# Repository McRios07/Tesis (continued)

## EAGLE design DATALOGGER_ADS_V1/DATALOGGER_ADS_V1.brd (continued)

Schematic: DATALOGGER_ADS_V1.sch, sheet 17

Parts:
C99, C103: 10uF; C0603
C100: 100uF; C1206
C101, C102, C104: 0.1uF; C0603
C116, C117: 1uF; C0603
R134, R136: 1K; R0603
R135, R138: 100; R0603
U7, U8: OPA350EA/2K5; DGK8_TEX
U12: REF5025AID; D8

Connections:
+5V: C117.1, U7.7 (V+), U8.7 (V+), U12.2 (VIN); also elsewhere on the board
GND: C99.2, C100.2, C102.2, C103.2, C104.2, C116.2, C117.2, U7.4 (V-), U8.4 (V-), U12.4 (GND); also elsewhere on the board
unnamed: C99.1, R134.1, U12.6 (VOUT)
unnamed: C100.1, R134.2, U7.3 (IN+)
unnamed: C116.1, U12.5 (TRIM/NR)
unnamed: C101.1, R136.1, U7.2 (IN-)
unnamed: C101.2, R135.1, U7.6 (OUTPUT)
unnamed: R138.1, U8.2 (IN-), U8.6 (OUTPUT)
VCOM3: R138.2; also elsewhere on the board
VCOMM3: C104.1, U8.3 (IN+); also elsewhere on the board
VREFP3: C102.1, C103.1, R135.2, R136.2; also elsewhere on the board

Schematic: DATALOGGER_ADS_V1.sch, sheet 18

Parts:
C105, C106, C107: 10uF; C0603
U9: ADS1278IPAPR; PAP64_7X7

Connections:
+1V8: C107.1, U9.26 (DVDD); also elsewhere on the board
+3V3: C106.1, U9.10 (CLKDIV_2), U9.22 (IOVDD_2), U9.23 (IOVDD), U9.31 (FORMAT1), U9.35 (!PWDN8), U9.36 (!PWDN7), U9.37 (!PWDN6), U9.38 (!PWDN5), U9.39 (!PWDN4), U9.40 (!PWDN3), U9.41 (!PWDN2), U9.42 (!PWDN1); also elsewhere on the board
+5V: C105.1, U9.5 (AVDD_2), U9.44 (AVDD_3), U9.53 (AVDD_4), U9.60 (AVDD); also elsewhere on the board
AINN3_1: U9.4 (AINN1); also elsewhere on the board
AINN3_2: U9.2 (AINN2); also elsewhere on the board
AINN3_3: U9.64 (AINN3); also elsewhere on the board
AINN3_4: U9.62 (AINN4); also elsewhere on the board
AINN3_5: U9.52 (AINN5)
AINN3_6: U9.50 (AINN6)
AINN3_7: U9.48 (AINN7)
AINN3_8: U9.46 (AINN8)
AINP3_1: U9.3 (AINP1); also elsewhere on the board
AINP3_2: U9.1 (AINP2); also elsewhere on the board
AINP3_3: U9.63 (AINP3); also elsewhere on the board
AINP3_4: U9.61 (AINP4); also elsewhere on the board
AINP3_5: U9.51 (AINP5)
AINP3_6: U9.49 (AINP6)
AINP3_7: U9.47 (AINP7)
AINP3_8: U9.45 (AINP8)
CLK3: U9.27 (CLKDIV); also elsewhere on the board
DOUT3_1: U9.20 (DOUT1); also elsewhere on the board
DOUT3_2: U9.19 (DOUT2); also elsewhere on the board
DOUT3_3: U9.18 (DOUT3); also elsewhere on the board
DOUT3_4: U9.17 (DOUT4); also elsewhere on the board
DOUT3_5: U9.16 (DOUT5)
DOUT3_6: U9.15 (DOUT6)
DOUT3_7: U9.14 (DOUT7)
DOUT3_8: U9.13 (DOUT8)
DRDY3: U9.29 (!DRDY/FSYNC); also elsewhere on the board
GND: C105.2, C106.2, C107.2, U9.6 (AGND_2), U9.7 (DGND_2), U9.8 (TEST0), U9.9 (TEST1), U9.12 (DIN), U9.21 (DGND_3), U9.24 (DGND_4), U9.25 (DGND), U9.30 (FORMAT2), U9.32 (FORMAT0), U9.33 (MODE1), U9.34 (MODE0), U9.43 (AGND_3), U9.54 (AGND_4), U9.57 (VREFN), U9.58 (AGND_5), U9.59 (AGND), U9.65 (EPAD); also elsewhere on the board
SCLK3: U9.28 (SCLK); also elsewhere on the board
SYNC3: U9.11 (!SYNC); also elsewhere on the board
VCOMM3: U9.55 (VCOM); also elsewhere on the board
VREFP3: U9.56 (VREFP); also elsewhere on the board

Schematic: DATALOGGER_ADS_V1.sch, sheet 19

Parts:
IC35, IC36, IC37, IC38, IC39, IC40, IC41, IC42: FODM217DV; SOIC127P700X220-4N
J3: 1985027
R147, R148, R149, R150, R151, R152, R153, R154, R155, R156, R157, R158, R159, R160, R161, R162: 220R; R0805

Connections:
+3V3: R148.2, R150.2, R152.2, R154.2, R156.2, R158.2, R160.2, R162.2; also elsewhere on the board
+5V: R147.1, R149.1, R151.1, R153.1, R155.1, R157.1, R159.1, R161.1; also elsewhere on the board
GND: IC35.3 (EMITTER), IC36.3 (EMITTER), IC37.3 (EMITTER), IC38.3 (EMITTER), IC39.3 (EMITTER), IC40.3 (EMITTER), IC41.3 (EMITTER), IC42.3 (EMITTER); also elsewhere on the board
LAZO1: IC35.4 (COLLECTOR), R148.1; also elsewhere on the board
LAZO2: IC36.4 (COLLECTOR), R150.1; also elsewhere on the board
LAZO3: IC37.4 (COLLECTOR), R152.1; also elsewhere on the board
LAZO4: IC38.4 (COLLECTOR), R154.1; also elsewhere on the board
LAZO5: IC39.4 (COLLECTOR), R156.1; also elsewhere on the board
LAZO6: IC40.4 (COLLECTOR), R158.1; also elsewhere on the board
LAZO7: IC41.4 (COLLECTOR), R160.1; also elsewhere on the board
LAZO8: IC42.4 (COLLECTOR), R162.1; also elsewhere on the board
LOOP1: IC35.2 (CATHODE), J3.1
LOOP2: IC36.2 (CATHODE), J3.2
LOOP3: IC37.2 (CATHODE), J3.3
LOOP4: IC38.2 (CATHODE), J3.4
LOOP5: IC39.2 (CATHODE), J3.5
LOOP6: IC40.2 (CATHODE), J3.6
LOOP7: IC41.2 (CATHODE), J3.7
LOOP8: IC42.2 (CATHODE), J3.8
unnamed: IC35.1 (ANODE), R147.2
unnamed: IC36.1 (ANODE), R149.2
unnamed: IC37.1 (ANODE), R151.2
unnamed: IC38.1 (ANODE), R153.2
unnamed: IC39.1 (ANODE), R155.2
unnamed: IC40.1 (ANODE), R157.2
unnamed: IC41.1 (ANODE), R159.2
unnamed: IC42.1 (ANODE), R161.2

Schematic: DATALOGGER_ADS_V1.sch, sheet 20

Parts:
IC31, IC32, IC33, IC34: TLV2771CDBVR; SOT95P280X145-5N
J4: 1989764; CONN_1989764_PXC
R49, R103, R133, R137: 50M; R0805
R53, R107, R164, R165: 1K; R0805
R143, R144, R145, R146: 100M; R0805

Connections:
+3V3: IC31.5 (VDD), IC32.5 (VDD), IC33.5 (VDD), IC34.5 (VDD); also elsewhere on the board
DOBLE1: IC31.3 (IN+), J4.1, R143.1
DOBLE2: IC32.3 (IN+), J4.2, R144.1
DOBLE3: IC33.3 (IN+), J4.3, R145.1
DOBLE4: IC34.3 (IN+), J4.4, R146.1
GND: IC31.2 (GND), IC32.2 (GND), IC33.2 (GND), IC34.2 (GND), R53.1, R107.1, R143.2, R144.2, R145.2, R146.2, R164.1, R165.1; also elsewhere on the board
INPUT17+: IC31.1 (OUT), R49.2; also elsewhere on the board
INPUT18+: IC32.1 (OUT), R103.2; also elsewhere on the board
INPUT19+: IC33.1 (OUT), R133.2; also elsewhere on the board
INPUT20+: IC34.1 (OUT), R137.2; also elsewhere on the board
unnamed: IC33.4 (IN-), R133.1, R165.2
unnamed: IC31.4 (IN-), R49.1, R53.2
unnamed: IC32.4 (IN-), R103.1, R107.2
unnamed: IC34.4 (IN-), R137.1, R164.2

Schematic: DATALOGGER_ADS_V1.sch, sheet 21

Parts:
IC27: D36V28F5-5V-3.2A
IC28: D24V5F1-1.8V-500MA; D24V5F1
IC29: D24V10F3-3.3V-1A
IC30, IC43: D24V25F5-5V-2.5A
J5: 1755736; CONN_1924305
U$4: D24V22F12-12V-2.2A; D24V22F12

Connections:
5V_2.5A: IC30.VOUT; also elsewhere on the board
5V_3.2A: IC27.6 (VOUT); also elsewhere on the board
+1V8: IC28.4 (VOUT); also elsewhere on the board
+3V3: IC29.5 (VOUT); also elsewhere on the board
+5V: IC43.VOUT; also elsewhere on the board
+12V: U$4.5 (VOUT); also elsewhere on the board
+24V: IC27.3 (VIN), IC28.2 (VIN), IC29.3 (VIN), IC30.VIN, IC43.VIN, J5.1, U$4.3 (VIN)
GND: IC27.4 (GND), IC27.5 (GND), IC28.3 (GND), IC29.4 (GND), IC30.GND@3 (GND), IC30.GND@4 (GND), IC43.GND@3 (GND), IC43.GND@4 (GND), J5.2, U$4.4 (GND); also elsewhere on the board

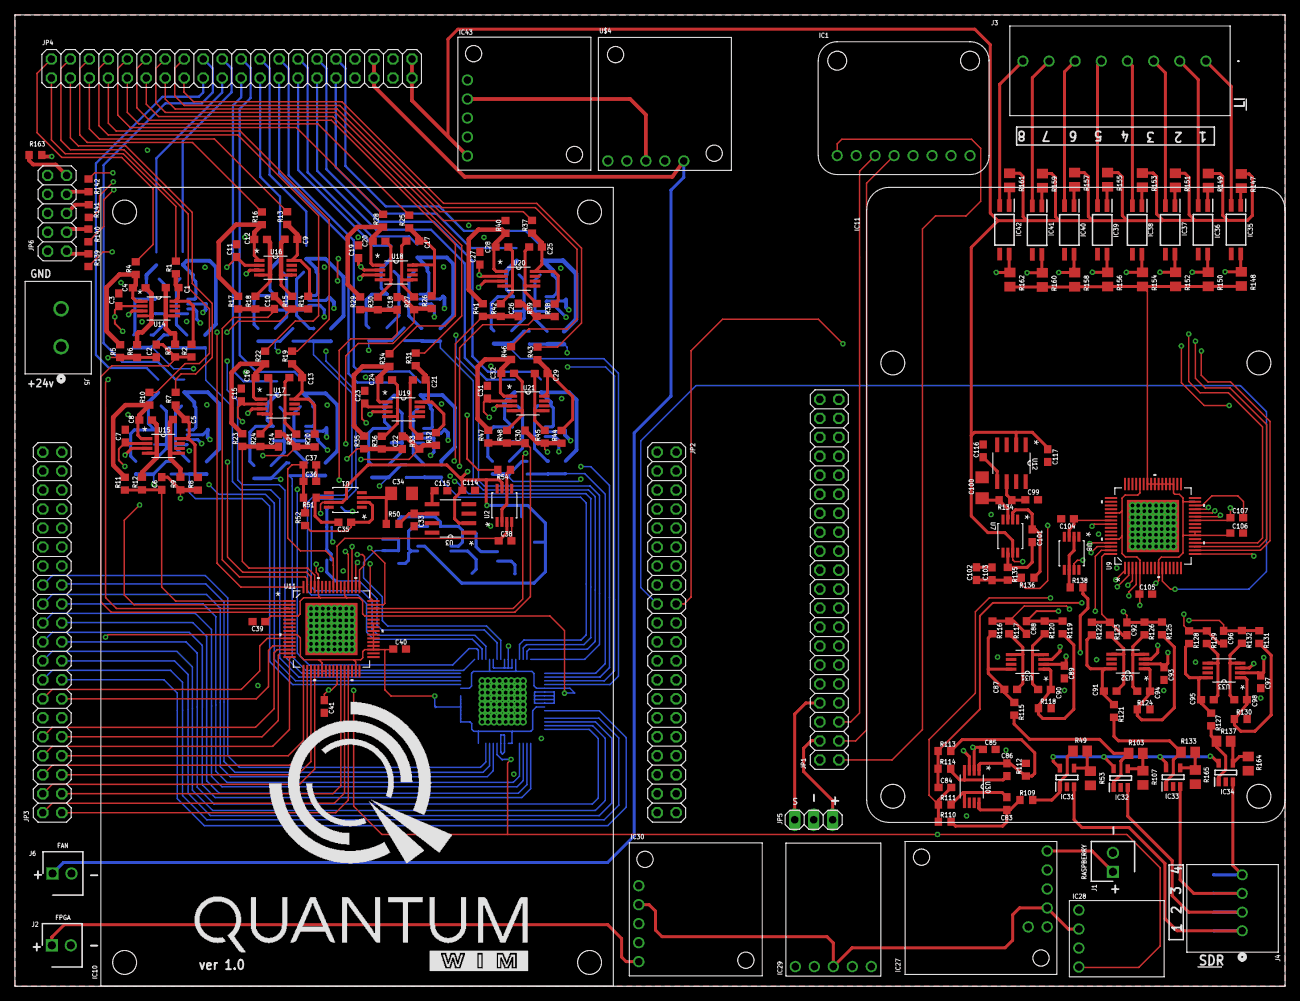
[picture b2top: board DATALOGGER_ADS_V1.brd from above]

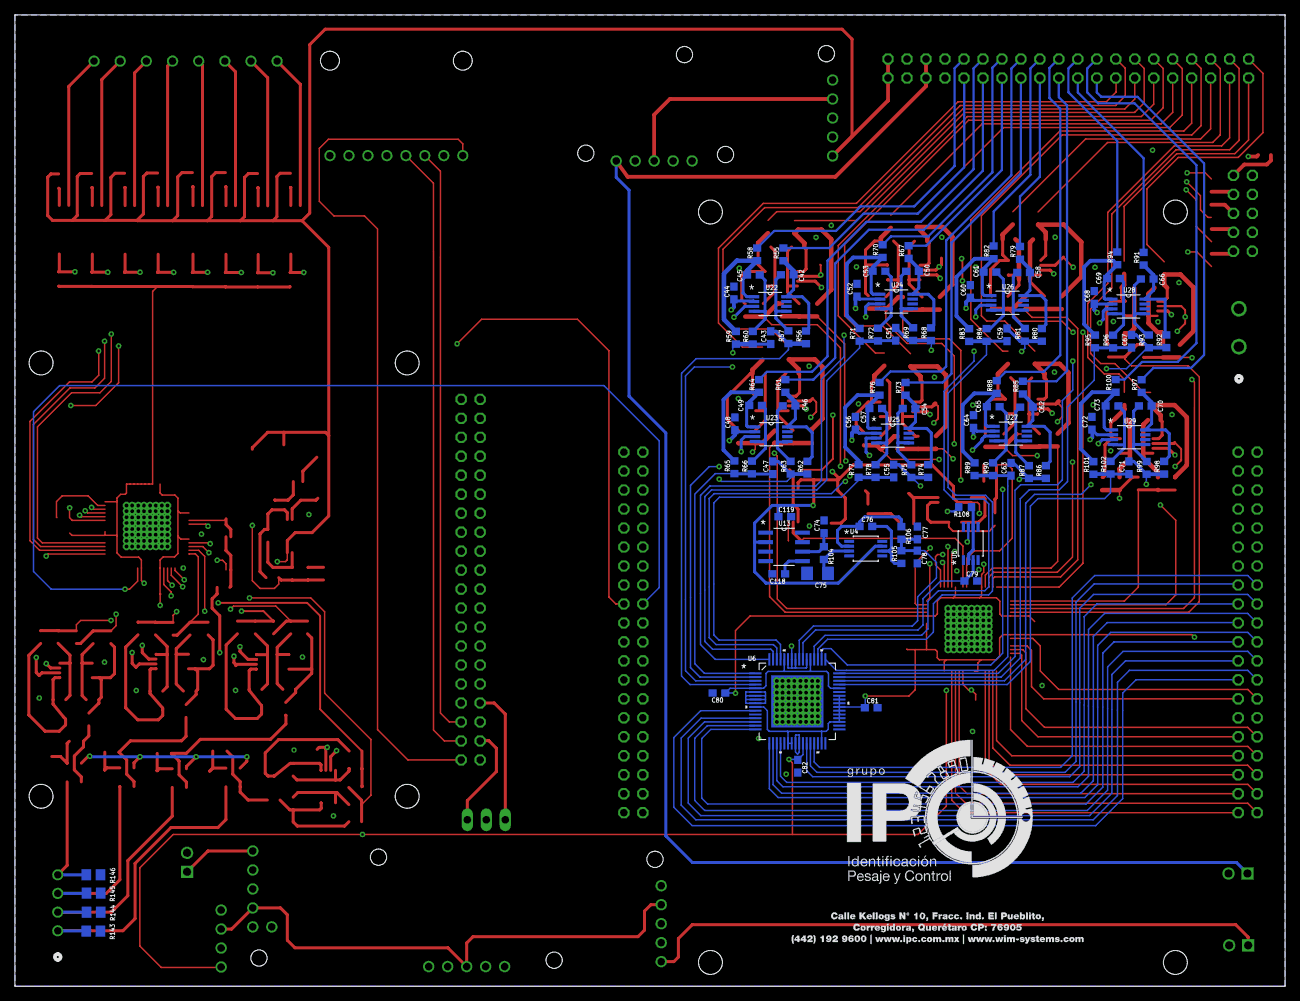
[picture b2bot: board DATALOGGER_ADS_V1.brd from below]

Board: 4 copper layers, 170.0 x 130.0 mm, 343 parts (111 on the bottom side), 269 nets.

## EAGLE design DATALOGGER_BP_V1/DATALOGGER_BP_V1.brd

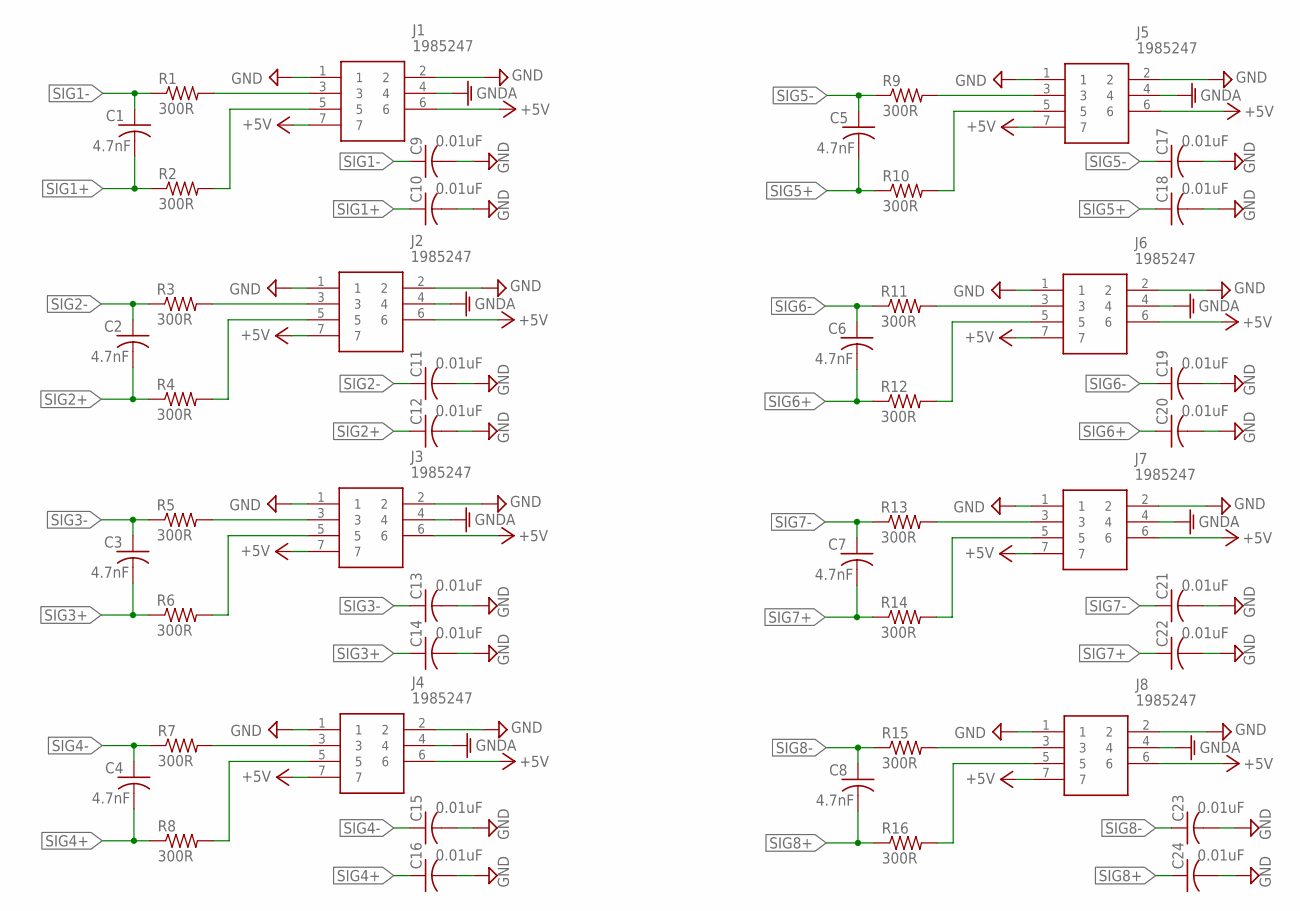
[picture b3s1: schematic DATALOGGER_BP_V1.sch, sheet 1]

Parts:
C1, C2, C3, C4, C5, C6, C7, C8: 4.7nF; C0805
C9, C10, C11, C12, C13, C14, C15, C16, C17, C18, C19, C20, C21, C22, C23, C24: 0.01uF; C0805
J1, J2, J3, J4, J5, J6, J7, J8: 1985247
R1, R2, R3, R4, R5, R6, R7, R8, R9, R10, R11, R12, R13, R14, R15, R16: 300R; R0805

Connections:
+5V: J1.6, J1.7, J2.6, J2.7, J3.6, J3.7, J4.6, J4.7, J5.6, J5.7, J6.6, J6.7, J7.6, J7.7, J8.6, J8.7; also elsewhere on the board
GND: C9.2, C10.2, C11.2, C12.2, C13.2, C14.2, C15.2, C16.2, C17.2, C18.2, C19.2, C20.2, C21.2, C22.2, C23.2, C24.2, J1.1, J1.2, J2.1, J2.2, J3.1, J3.2, J4.1, J4.2, J5.1, J5.2, J6.1, J6.2, J7.1, J7.2, J8.1, J8.2; also elsewhere on the board
GNDA: J1.4, J2.4, J3.4, J4.4, J5.4, J6.4, J7.4, J8.4; also elsewhere on the board
unnamed: J1.3, R1.2
unnamed: J1.5, R2.2
unnamed: J2.3, R3.2
unnamed: J2.5, R4.2
unnamed: J3.3, R5.2
unnamed: J3.5, R6.2
unnamed: J4.3, R7.2
unnamed: J4.5, R8.2
unnamed: J5.3, R9.2
unnamed: J5.5, R10.2
unnamed: J6.3, R11.2
unnamed: J6.5, R12.2
unnamed: J7.3, R13.2
unnamed: J7.5, R14.2
unnamed: J8.3, R15.2
unnamed: J8.5, R16.2
SIG1+: C1.2, C10.1, R2.1; also elsewhere on the board
SIG1-: C1.1, C9.1, R1.1; also elsewhere on the board
SIG2+: C2.2, C12.1, R4.1; also elsewhere on the board
SIG2-: C2.1, C11.1, R3.1; also elsewhere on the board
SIG3+: C3.2, C14.1, R6.1; also elsewhere on the board
SIG3-: C3.1, C13.1, R5.1; also elsewhere on the board
SIG4+: C4.2, C16.1, R8.1; also elsewhere on the board
SIG4-: C4.1, C15.1, R7.1; also elsewhere on the board
SIG5+: C5.2, C18.1, R10.1; also elsewhere on the board
SIG5-: C5.1, C17.1, R9.1; also elsewhere on the board
SIG6+: C6.2, C20.1, R12.1; also elsewhere on the board
SIG6-: C6.1, C19.1, R11.1; also elsewhere on the board
SIG7+: C7.2, C22.1, R14.1; also elsewhere on the board
SIG7-: C7.1, C21.1, R13.1; also elsewhere on the board
SIG8+: C8.2, C24.1, R16.1; also elsewhere on the board
SIG8-: C8.1, C23.1, R15.1; also elsewhere on the board

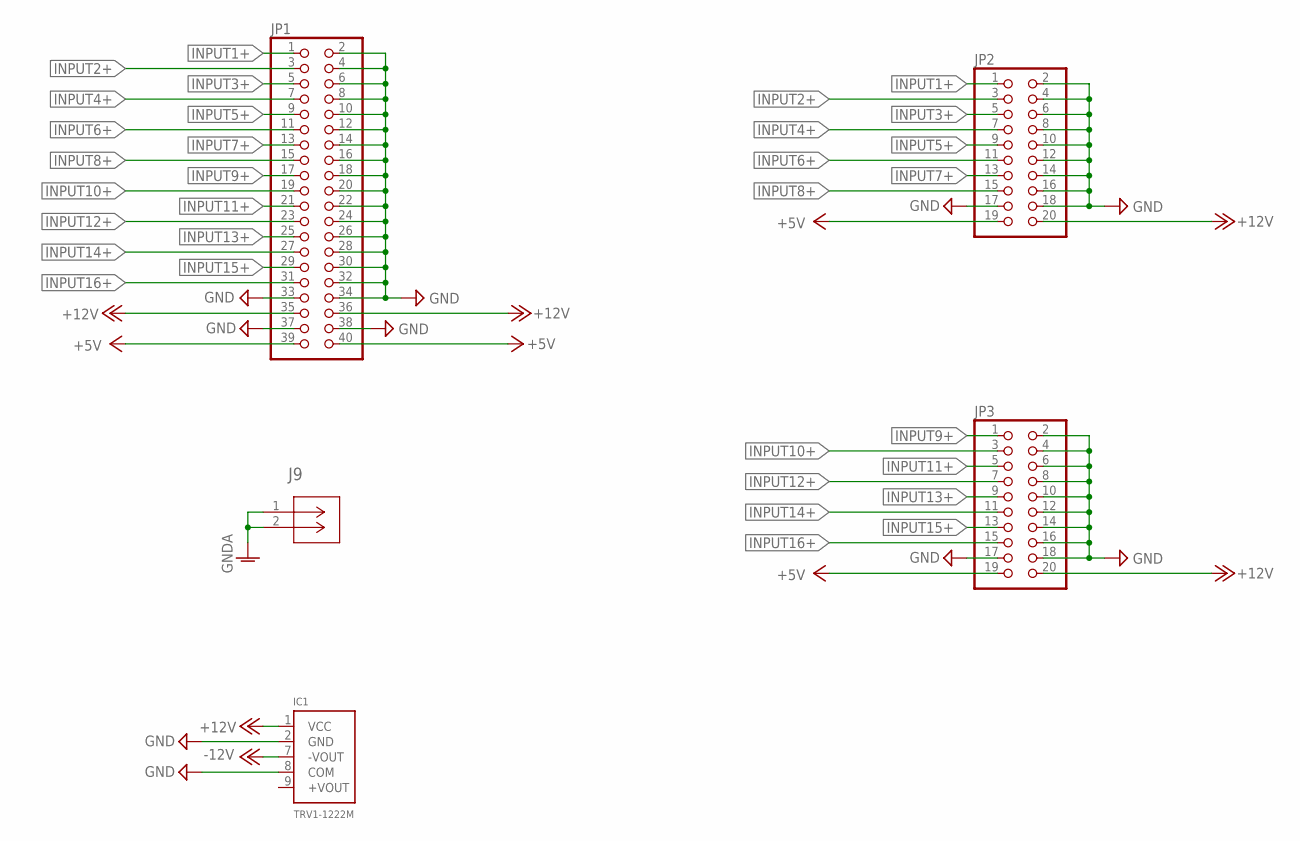
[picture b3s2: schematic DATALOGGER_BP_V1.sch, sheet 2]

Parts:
IC1: TRV1-1222M
J9: 1755736; CONN_1924305
JP1: PINHD-2X20; 2X20
JP2, JP3: PINHD-2X10; 2X10

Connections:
+5V: JP1.39, JP1.40, JP2.19, JP3.19; also elsewhere on the board
+12V: IC1.1 (VCC), JP1.35, JP1.36, JP2.20, JP3.20; also elsewhere on the board
-12V: IC1.7 (-VOUT); also elsewhere on the board
GND: IC1.2 (GND), IC1.8 (COM), JP1.2, JP1.4, JP1.6, JP1.8, JP1.10, JP1.12, JP1.14, JP1.16, JP1.18, JP1.20, JP1.22, JP1.24, JP1.26, JP1.28, JP1.30, JP1.32, JP1.33, JP1.34, JP1.37, JP1.38, JP2.2, JP2.4, JP2.6, JP2.8, JP2.10, JP2.12, JP2.14, JP2.16, JP2.17, JP2.18, JP3.2, JP3.4, JP3.6, JP3.8, JP3.10, JP3.12, JP3.14, JP3.16, JP3.17, JP3.18; also elsewhere on the board
GNDA: J9.1, J9.2; also elsewhere on the board
INPUT1+: JP1.1, JP2.1; also elsewhere on the board
INPUT2+: JP1.3, JP2.3; also elsewhere on the board
INPUT3+: JP1.5, JP2.5; also elsewhere on the board
INPUT4+: JP1.7, JP2.7; also elsewhere on the board
INPUT5+: JP1.9, JP2.9; also elsewhere on the board
INPUT6+: JP1.11, JP2.11; also elsewhere on the board
INPUT7+: JP1.13, JP2.13; also elsewhere on the board
INPUT8+: JP1.15, JP2.15; also elsewhere on the board
INPUT9+: JP1.17, JP3.1
INPUT10+: JP1.19, JP3.3
INPUT11+: JP1.21, JP3.5
INPUT12+: JP1.23, JP3.7
INPUT13+: JP1.25, JP3.9
INPUT14+: JP1.27, JP3.11
INPUT15+: JP1.29, JP3.13
INPUT16+: JP1.31, JP3.15

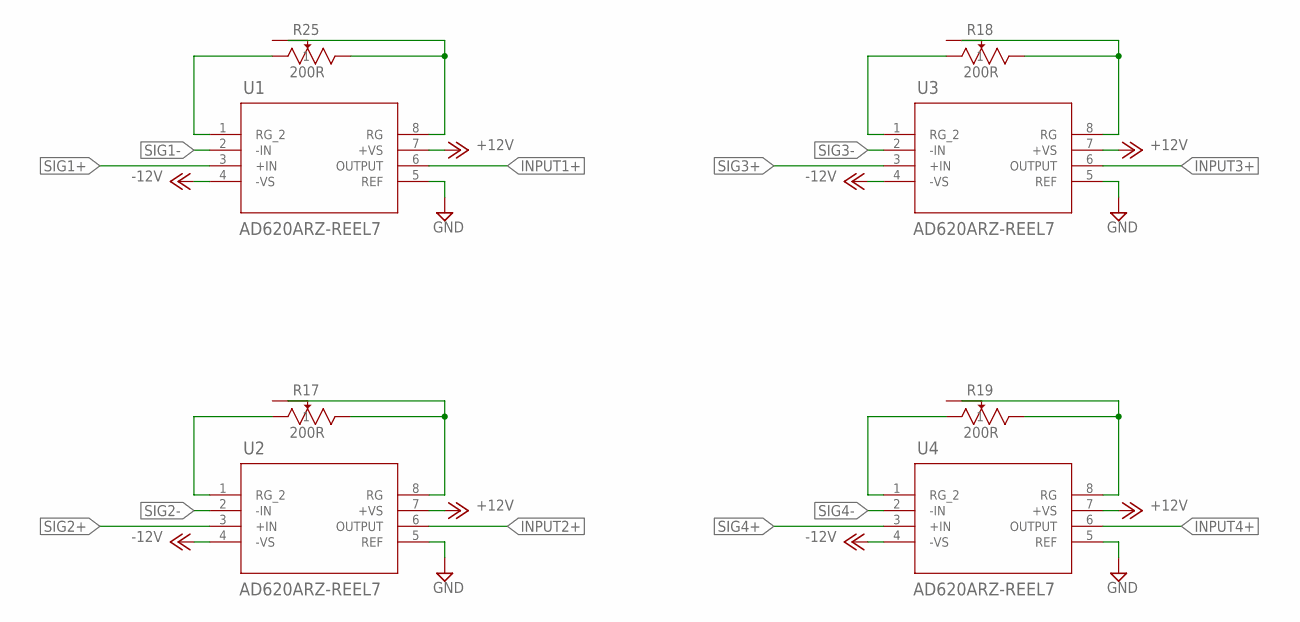
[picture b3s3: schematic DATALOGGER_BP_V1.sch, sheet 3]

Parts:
R17, R18, R19, R25: 200R; RES3_22A_TTE
U1, U2, U3, U4: AD620ARZ-REEL7; R_8_ADI

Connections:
+12V: U1.7 (+VS), U2.7 (+VS), U3.7 (+VS), U4.7 (+VS); also elsewhere on the board
-12V: U1.4 (-VS), U2.4 (-VS), U3.4 (-VS), U4.4 (-VS); also elsewhere on the board
GND: U1.5 (REF), U2.5 (REF), U3.5 (REF), U4.5 (REF); also elsewhere on the board
INPUT1+: U1.6 (OUTPUT); also elsewhere on the board
INPUT2+: U2.6 (OUTPUT); also elsewhere on the board
INPUT3+: U3.6 (OUTPUT); also elsewhere on the board
INPUT4+: U4.6 (OUTPUT); also elsewhere on the board
unnamed: R25.1, U1.1 (RG_2)
unnamed: R25.2, R25.3, U1.8 (RG)
unnamed: R17.1, U2.1 (RG_2)
unnamed: R17.2, R17.3, U2.8 (RG)
unnamed: R18.1, U3.1 (RG_2)
unnamed: R18.2, R18.3, U3.8 (RG)
unnamed: R19.1, U4.1 (RG_2)
unnamed: R19.2, R19.3, U4.8 (RG)
SIG1+: U1.3 (+IN); also elsewhere on the board
SIG1-: U1.2 (-IN); also elsewhere on the board
SIG2+: U2.3 (+IN); also elsewhere on the board
SIG2-: U2.2 (-IN); also elsewhere on the board
SIG3+: U3.3 (+IN); also elsewhere on the board
SIG3-: U3.2 (-IN); also elsewhere on the board
SIG4+: U4.3 (+IN); also elsewhere on the board
SIG4-: U4.2 (-IN); also elsewhere on the board

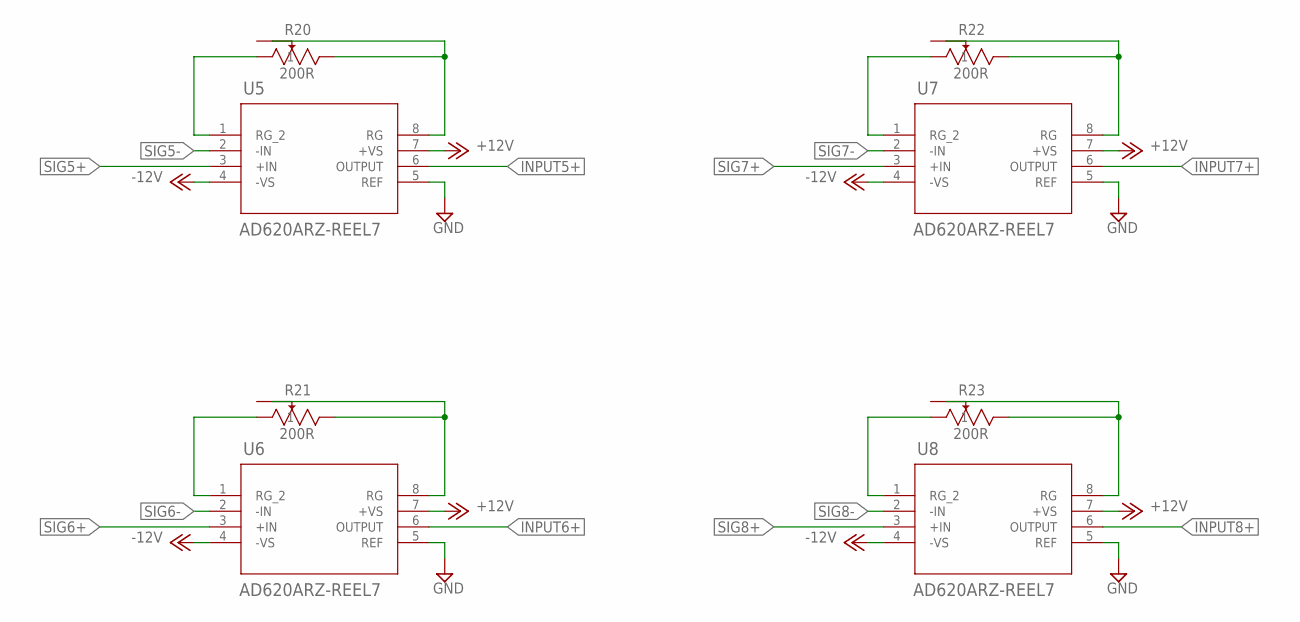
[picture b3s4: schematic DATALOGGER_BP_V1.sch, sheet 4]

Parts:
R20, R21, R22, R23: 200R; RES3_22A_TTE
U5, U6, U7, U8: AD620ARZ-REEL7; R_8_ADI

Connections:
+12V: U5.7 (+VS), U6.7 (+VS), U7.7 (+VS), U8.7 (+VS); also elsewhere on the board
-12V: U5.4 (-VS), U6.4 (-VS), U7.4 (-VS), U8.4 (-VS); also elsewhere on the board
GND: U5.5 (REF), U6.5 (REF), U7.5 (REF), U8.5 (REF); also elsewhere on the board
INPUT5+: U5.6 (OUTPUT); also elsewhere on the board
INPUT6+: U6.6 (OUTPUT); also elsewhere on the board
INPUT7+: U7.6 (OUTPUT); also elsewhere on the board
INPUT8+: U8.6 (OUTPUT); also elsewhere on the board
unnamed: R20.1, U5.1 (RG_2)
unnamed: R20.2, R20.3, U5.8 (RG)
unnamed: R21.1, U6.1 (RG_2)
unnamed: R21.2, R21.3, U6.8 (RG)
unnamed: R22.1, U7.1 (RG_2)
unnamed: R22.2, R22.3, U7.8 (RG)
unnamed: R23.1, U8.1 (RG_2)
unnamed: R23.2, R23.3, U8.8 (RG)
SIG5+: U5.3 (+IN); also elsewhere on the board
SIG5-: U5.2 (-IN); also elsewhere on the board
SIG6+: U6.3 (+IN); also elsewhere on the board
SIG6-: U6.2 (-IN); also elsewhere on the board
SIG7+: U7.3 (+IN); also elsewhere on the board
SIG7-: U7.2 (-IN); also elsewhere on the board
SIG8+: U8.3 (+IN); also elsewhere on the board
SIG8-: U8.2 (-IN); also elsewhere on the board

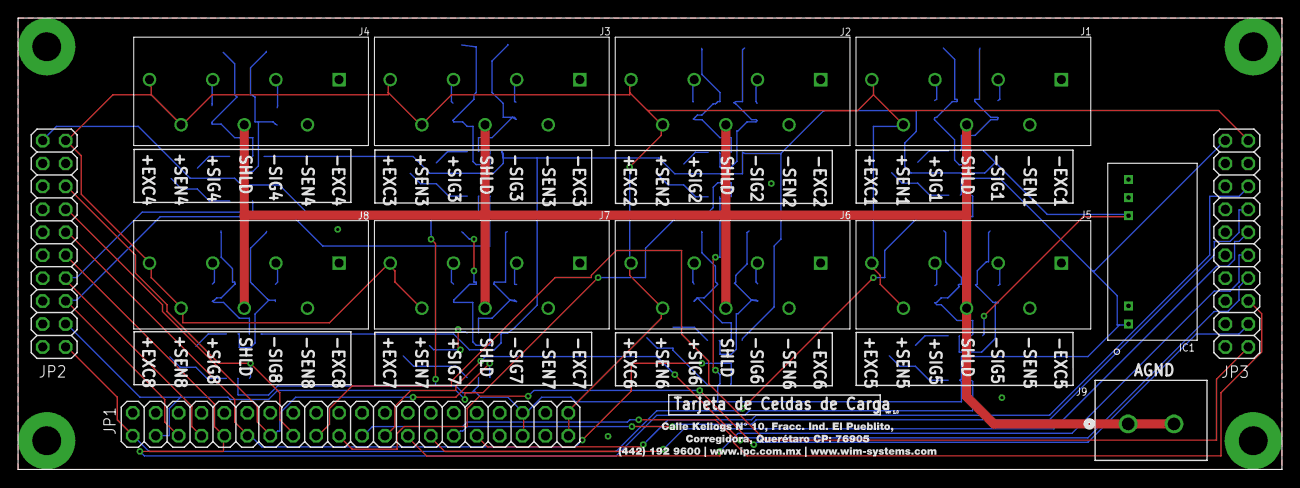
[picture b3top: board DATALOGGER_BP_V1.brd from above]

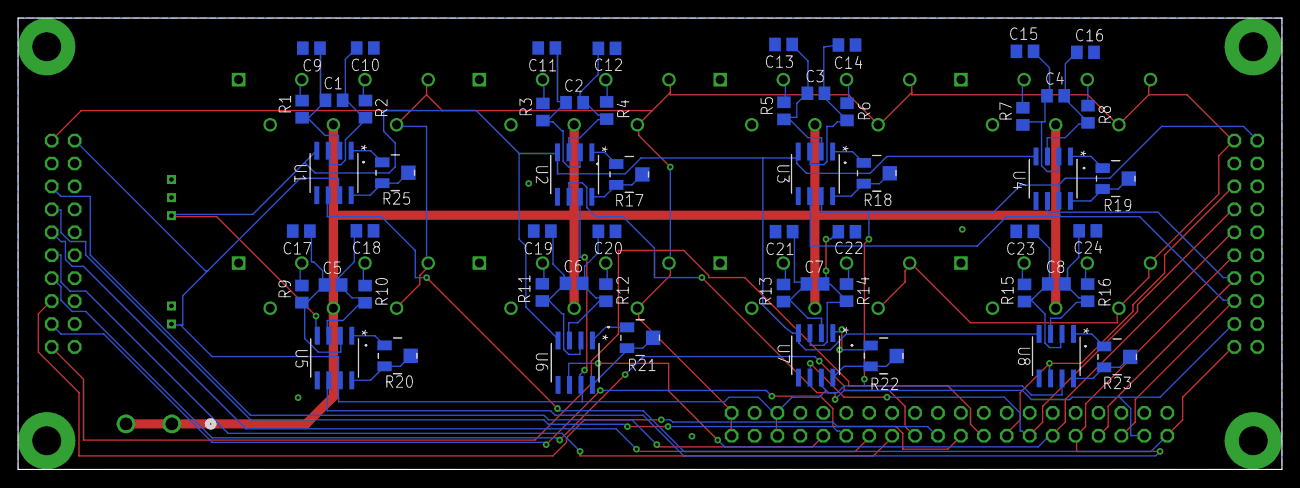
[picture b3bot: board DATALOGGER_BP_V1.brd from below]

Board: 2 copper layers, 140.0 x 50.0 mm, 69 parts (56 on the bottom side), 69 nets.

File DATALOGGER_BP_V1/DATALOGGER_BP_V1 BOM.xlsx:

|  |  | DATALOGGER_BP_V1 BOM
Item # | *Designator | *Qty | Manufacturer | *Mfg Part # | Description / Value | *Package/Footprint | Type | Your Instructions / Notes
1 | JP2, JP3 | 2 | Generic | Generic | Pin header | 2X10 | PTH
2 | JP1 | 1 | Generic | Generic | Pin header | 2X20 | PTH
3 | C1, C2, C3, C4, C5, C6, C7, C8 | 8 | Würth Elektronik | 885012207037 | 4700pF ±10% 16V Ceramic Capacitor X7R 0805 (2012 Metric) | 0805 | SMD | https://www.digikey.com/en/products/detail/w%C3%BCrth-elektr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
4 | R1, R2, R3, R4, R5, R6, R7, R8, R9, R10, R11, R12, R13, R14, R15, R16 | 16 | Yageo | RC0805FR-07300RL | 300 Ohms ±1% 0.125W, 1/8W Chip Resistor 0805 (2012 Metric) Moisture Resistant T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 | 0805 | SMD | https://www.digikey.com/en/products/detail/yageo/RC0805FR-07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
5 | C9, C10, C11, C12, C13, C14, C15, C16, C17, C18, C19, C20, C21, C22, C23, C24 | 16 | Würth Elektronik | 885012007009 | 10000pF ±5% 10V Ceramic Capacitor C0G, NP0 0805 (2012 Metric) | 0805 | SMD | https://www.digikey.com/en/products/detail/w%C3%BCrth-elektr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
6 | J1, J2, J3, J4, J5, J6, J7, J7 | 8 | Phoenix Contact | 1985247 | TERM BLOCK 7POS 45DEG 3.5MM PCB | 1985247 | PTH | https://www.digikey.com.mx/en/products/detail/phoenix-contac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
7 | R17, R18, R19, R20, R21, R22, R23, R25 | 8 | TT Electronics/BI | 22AR200LFTR | TRIMMER 200OHM 0.125W J LEAD TOP |  | SMD | https://www.digikey.com.mx/es/products/detail/tt-electronics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
8 | U1, U2, U3, U4, U5, U6, U7, U8 | 8 | Analog Devices Inc. | AD620ARZ-REEL7 | IC INST AMP 1 CIRCUIT 8SOIC | 8-SOIC | SMD | https://www.digikey.com/en/products/detail/analog-devices-in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
9 | IC1 | 1 | Traco Power | TRV 1-1222M | Isolated Module DC DC Converter 2 Output 12V -12V 42mA, 42mA 9.6V - 14.4V Input | TRV 1-1222M | PTH | https://www.digikey.com/en/products/detail/traco-power/TRV-1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
10 | J9 | 1 | Phoenix Contact | 1755736 | 2 Position Terminal Block Header, Male Pins, Shrouded (4 Side) 0.200" (5.08mm) 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 | 1755736 | PTH | https://www.digikey.com.mx/en/products/detail/phoenix-contac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
 |  |  |  |  |  |  |  | and for the item 10, I want the terminal block plug
 |  |  |  |  |  |  |  | https://www.digikey.com.mx/en/products/detail/phoenix-contac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

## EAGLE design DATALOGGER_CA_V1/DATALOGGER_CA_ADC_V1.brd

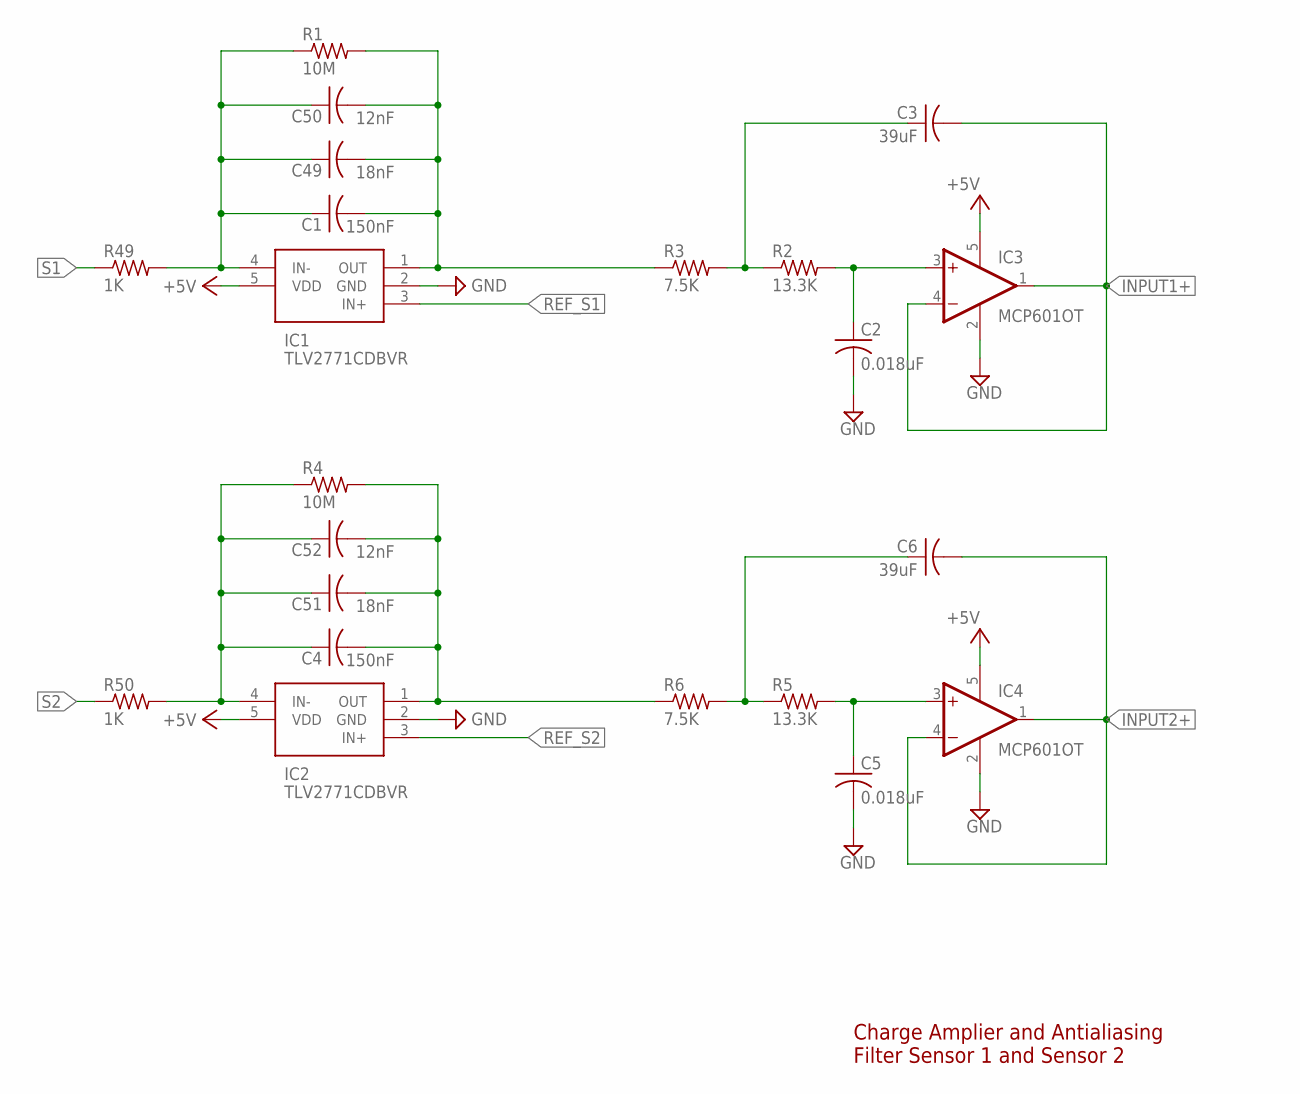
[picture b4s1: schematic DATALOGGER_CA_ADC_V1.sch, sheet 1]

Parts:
C1, C4: 150nF; C0805
C2, C5: 0.018uF; C0805
C3, C6: 39uF; C0805
C49, C51: 18nF; C0805
C50, C52: 12nF; C0805
IC1, IC2: TLV2771CDBVR; SOT95P280X145-5N
IC3, IC4: MCP601OT; SOT23-5
R1, R4: 10M; R0805
R2, R5: 13.3K; R0805
R3, R6: 7.5K; R0805
R49, R50: 1K; R0805

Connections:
+5V: IC1.5 (VDD), IC2.5 (VDD), IC3.5 (V+), IC4.5 (V+); also elsewhere on the board
GND: C2.2, C5.2, IC1.2 (GND), IC2.2 (GND), IC3.2 (V-), IC4.2 (V-); also elsewhere on the board
INPUT1+: C3.2, IC3.1 (OUT), IC3.4 (-IN); also elsewhere on the board
INPUT2+: C6.2, IC4.1 (OUT), IC4.4 (-IN); also elsewhere on the board
unnamed: C1.2, C49.2, C50.2, IC1.1 (OUT), R1.2, R3.1
unnamed: C2.1, IC3.3 (+IN), R2.2
unnamed: C3.1, R2.1, R3.2
unnamed: C4.2, C51.2, C52.2, IC2.1 (OUT), R4.2, R6.1
unnamed: C5.1, IC4.3 (+IN), R5.2
unnamed: C6.1, R5.1, R6.2
unnamed: C4.1, C51.1, C52.1, IC2.4 (IN-), R4.1, R50.2
unnamed: C1.1, C49.1, C50.1, IC1.4 (IN-), R1.1, R49.2
REF_S1: IC1.3 (IN+); also elsewhere on the board
REF_S2: IC2.3 (IN+); also elsewhere on the board
S1: R49.1; also elsewhere on the board
S2: R50.1; also elsewhere on the board

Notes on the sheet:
Charge Amplier and Antialiasing Filter Sensor 1 and Sensor 2

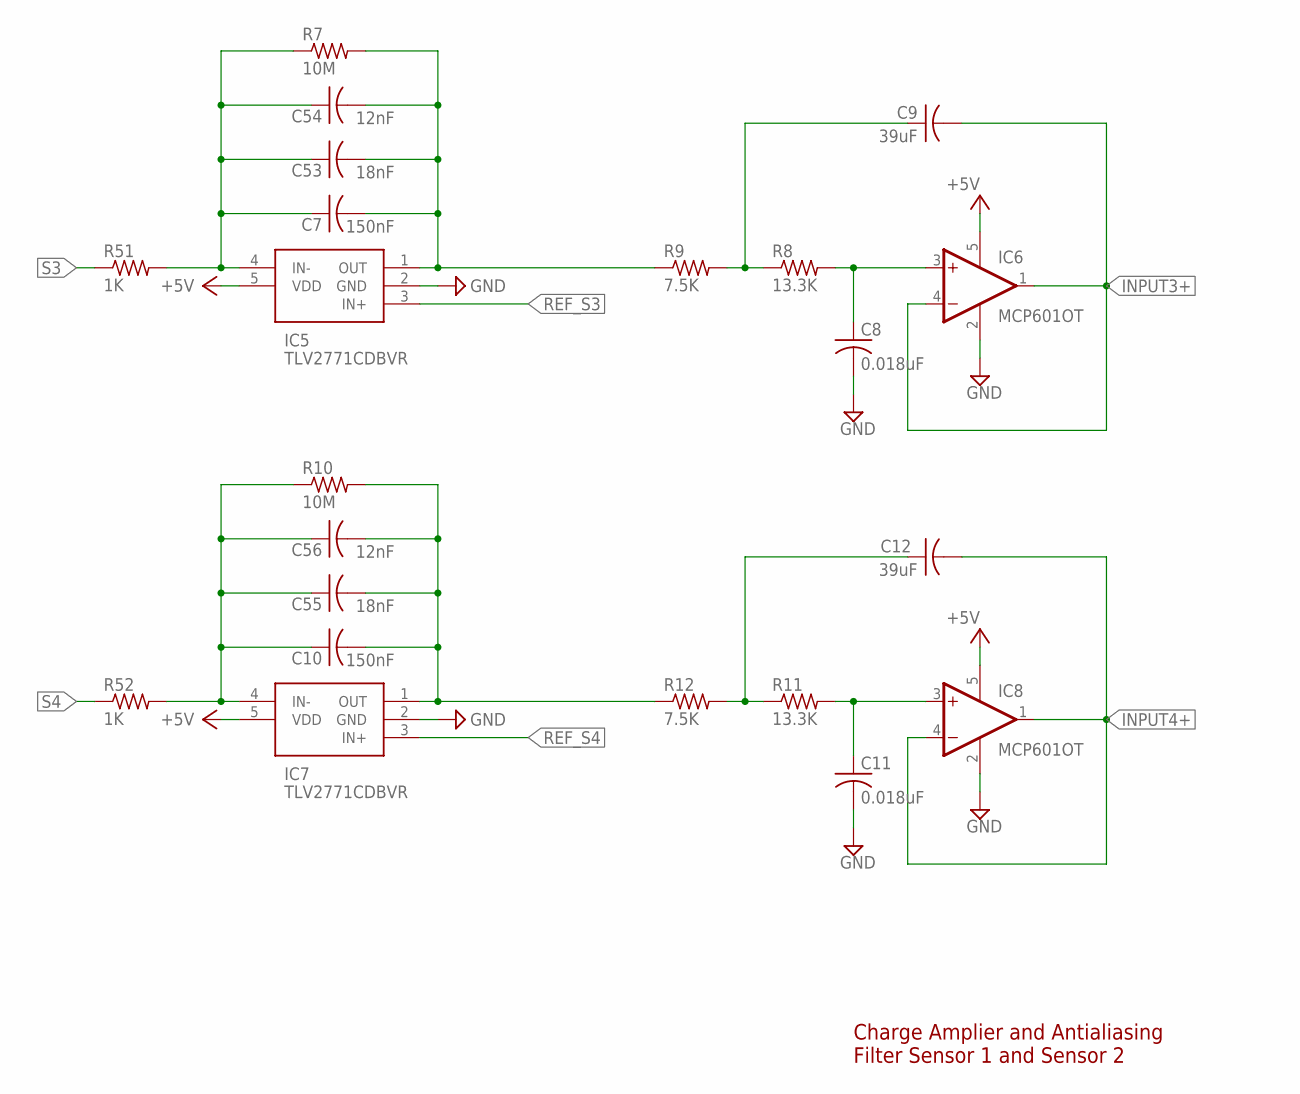
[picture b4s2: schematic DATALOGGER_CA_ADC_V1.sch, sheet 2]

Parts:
C7, C10: 150nF; C0805
C8, C11: 0.018uF; C0805
C9, C12: 39uF; C0805
C53, C55: 18nF; C0805
C54, C56: 12nF; C0805
IC5, IC7: TLV2771CDBVR; SOT95P280X145-5N
IC6, IC8: MCP601OT; SOT23-5
R7, R10: 10M; R0805
R8, R11: 13.3K; R0805
R9, R12: 7.5K; R0805
R51, R52: 1K; R0805

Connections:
+5V: IC5.5 (VDD), IC6.5 (V+), IC7.5 (VDD), IC8.5 (V+); also elsewhere on the board
GND: C8.2, C11.2, IC5.2 (GND), IC6.2 (V-), IC7.2 (GND), IC8.2 (V-); also elsewhere on the board
INPUT3+: C9.2, IC6.1 (OUT), IC6.4 (-IN); also elsewhere on the board
INPUT4+: C12.2, IC8.1 (OUT), IC8.4 (-IN); also elsewhere on the board
unnamed: C7.2, C53.2, C54.2, IC5.1 (OUT), R7.2, R9.1
unnamed: C8.1, IC6.3 (+IN), R8.2
unnamed: C9.1, R8.1, R9.2
unnamed: C10.2, C55.2, C56.2, IC7.1 (OUT), R10.2, R12.1
unnamed: C11.1, IC8.3 (+IN), R11.2
unnamed: C12.1, R11.1, R12.2
unnamed: C7.1, C53.1, C54.1, IC5.4 (IN-), R7.1, R51.2
unnamed: C10.1, C55.1, C56.1, IC7.4 (IN-), R10.1, R52.2
REF_S3: IC5.3 (IN+); also elsewhere on the board
REF_S4: IC7.3 (IN+); also elsewhere on the board
S3: R51.1; also elsewhere on the board
S4: R52.1; also elsewhere on the board

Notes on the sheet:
Charge Amplier and Antialiasing Filter Sensor 1 and Sensor 2
